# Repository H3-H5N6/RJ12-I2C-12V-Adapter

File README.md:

# Beschreibung

Platine für die Umsetzung von 2x4- und 2x2-Pins auf 2x RJ 12 

# Schaltplan

# Bestückungsplan

# ChangeLog
## v1.0
* erste Version

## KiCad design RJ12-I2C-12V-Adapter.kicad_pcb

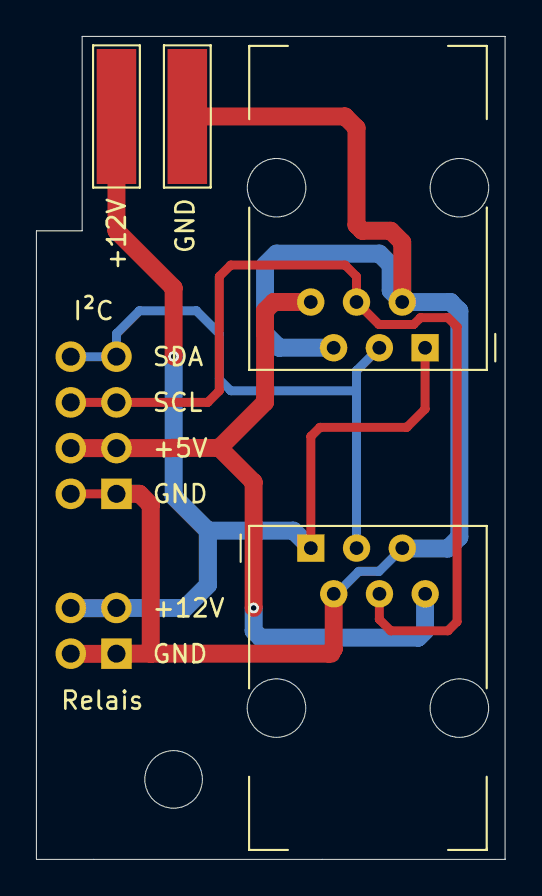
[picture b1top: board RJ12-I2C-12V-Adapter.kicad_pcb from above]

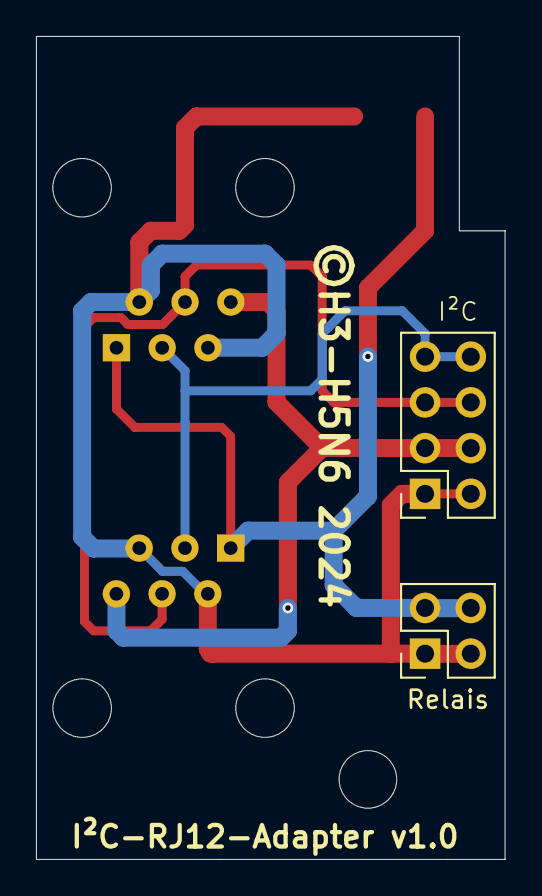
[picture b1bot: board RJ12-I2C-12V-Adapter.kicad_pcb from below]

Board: 2 copper layers, 26.0 x 45.7 mm, 9 parts (2 on the bottom side), 5 nets.

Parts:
H2: MountingHole; MountingHole_3.2mm_M3
J1, J2: 6P6C; RJ12_Amphenol_54601_Light
J10: I²C; PinSocket_2x04_P2.54mm_Vertical
J11: Relais; PinSocket_2x02_P2.54mm_Vertical
J12: +12V; Pad_7.5x2.2mm
J13: GND; Pad_7.5x2.2mm
Tx1: ©H3-H5N6 2024; Text
Tx2: I²C-RJ12-Adapter v1.0; Text

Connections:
+5V: J1.6, J2.6, J10.3, J10.4
+12V: J1.1, J2.1, J11.3, J11.4, J12.1
/SCL: J1.4, J2.4, J10.5, J10.6
/SDA: J1.3, J2.3, J10.7, J10.8
GND: J1.2, J1.5, J2.2, J2.5, J10.1, J10.2, J11.1, J11.2, J13.1

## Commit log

2024-04-05 Initial
2024-04-05 Extra Anschlüsse für 12V/GND, RJ12 ganz an den Rand geschoben
2024-04-05 Beschreibung J10/J10 geändert
